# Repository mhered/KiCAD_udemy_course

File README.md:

# README.md

This repository contains [my course notes](./notes/KiCAD_notes.md) from the Udemy course [KiCAD like a Pro](https://www.udemy.com/course/kicad-like-a-pro-3e/) by Dr Peter Dalmaris, as well as several beginner friendly KiCAD projects (some of which are inspired in the course)

| Image                                                        | Name                                                         | Description                                                  | Source                                                       |
| ------------------------------------------------------------ | ------------------------------------------------------------ | ------------------------------------------------------------ | ------------------------------------------------------------ |
|            | [LED Torch](./projects/01_LED_torch/)                        | First basic PBC. Project #1 from the Udemy course [KiCAD like a Pro](https://www.udemy.com/course/kicad-like-a-pro-3e/) by Dr Peter Dalmaris | [KiCAD like a Pro](https://www.udemy.com/course/kicad-like-a-pro-3e/) |
|  | [Breadboard Power Supply](./projects/02_breadboard_power_supply/) | Project #2 from the Udemy course [KiCAD like a Pro](https://www.udemy.com/course/kicad-like-a-pro-3e/) by Dr Peter Dalmaris | [KiCAD like a Pro](https://www.udemy.com/course/kicad-like-a-pro-3e/) |
|  | [Tiny Solar Supply](./projects/03_tiny_solar_supply/)        | Project #3 from the Udemy course [KiCAD like a Pro](https://www.udemy.com/course/kicad-like-a-pro-3e/) by Dr Peter Dalmaris | [KiCAD like a Pro](https://www.udemy.com/course/kicad-like-a-pro-3e/) |
|  | [MCU Datalogger](./projects/04_MCU_datalogger/)              | Project #4 from the Udemy course [KiCAD like a Pro](https://www.udemy.com/course/kicad-like-a-pro-3e/) by Dr Peter Dalmaris | [KiCAD like a Pro](https://www.udemy.com/course/kicad-like-a-pro-3e/) |
|              | [Kinect Lite](./projects/05_kinect_lite/)                    | Hacking the Kinect - inspired by a post by Weekend Robotics from 2019 on how to turn an old Kinect into a low cost and compact USB-C powered RGBD sensor | [Weekend Robotics]( https://medium.com/robotics-weekends/how-to-turn-old-kinect-into-a-compact-usb-powered-rgbd-sensor-f23d58e10eb0) and [vojtapl's Github](https://github.com/vojtapl/xbox360-kinect-lite) |
|         | [Pico IoT Thingy](./projects/06_pico_IoT_thingy/)            | Raspberry PICO IoT device on 4-layer PCB with sensors and more b- based on a YouTube tutorial by morten | [YouTube tutorial ](https://www.youtube.com/watch?v=tCulctQqdhM) by morten |
|                 | [MSPM0](./projects/07_MSPM0/)                                | Texas Instruments MSPM0-based hardware (USB, power, MCU, peripherals) based on a YouTube tutorial by Phil's Lab | [YouTube tutorial](https://www.youtube.com/watch?v=O-zNn5k5Bn4) by Phil's Lab |
|                   | [Reskin](./projects/08_reskin/)                              | 5X Reskin pressure sensor for robotics                       | [raunaqbhirangi's Github](https://github.com/raunaqbhirangi/reskin_sensor/tree/main/circuits) |

### ⚠️ Libraries included

This repository follows (mostly) [these recommendations](./notes/recommended_libraries_setup_in_KiCAD_repo.md) to facilitate that everything needed to replicate these projects travels with the repo 

### ⚠️ Git LFS Required

This repository uses [Git Large File Storage (Git LFS)](https://git-lfs.com/) to handle large files (mainly for CAD models, and zipped gerber files).

If you clone the repo without Git LFS, large files will appear as tiny pointer files instead of the real content.

### Setup
1. Install Git LFS on your system:

   ```bash
   sudo apt install git-lfs
   ```

2. Run once on your machine to set it up for your user account:
   ```bash
   git lfs install
   ```

3. Clone the repository as usual:

   ```bash
   git clone https://github.com/mhered/KiCAD_udemy_course.git
   ```

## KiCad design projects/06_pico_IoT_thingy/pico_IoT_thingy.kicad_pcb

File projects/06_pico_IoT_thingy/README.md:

# README.md

[TOC]

Design of a Raspberry PICO IoT device on 4-layer PCB with sensors and more. Ref. https://www.youtube.com/watch?v=tCulctQqdhM by morten

Features:

* Raspberry Pi Pico (W)
* RS485 / MOD-bus interface
*  DIP-switch for MOD-bus address selection 
* SHT31-DIS high precision temperature and humidity sensor. I used P version (with protective film for reflow)
* QWIIC connector 
* Reset Button  
* User Button 
* User RGB LED 
* 2x5 pin SPI bus expansion header   
* Power relay (230V - 16A)      
* Wide range input voltage +8V to 24V DC 

For the mechanical side of things:

* 4-layer board design
* Size 80x80mm
* 4 x 3.2mm mounting holes 

## My notes on components

TRACO Power TSR-1 2450 - DC-DC step-down (buck) regulator (replaces 78xx linear regulators) with a single 5V output at up to 1A

DC power jack > takes nominal 12V but accepts a wide range of input voltage

1A polyfuse to protect input - 1.1A hold current polyfuse > selected MF-R110 (TH) / MF-SM100-2 (SMT)

diode 24V tranzorb (used **SMAJ24A**)

3.3V bar: 

* Check out this guide [Hardware design with RP2040](https://pip-assets.raspberrypi.com/categories/814-rp2040/documents/RP-008279-DS-1-hardware-design-with-rp2040.pdf)  guide ([local copy](./assets/RP-008279-DS-1-hardware-design-with-rp2040.pdf))
* LDO for 3.3.V - TLV1117-33IDCYR 800mA Low-Dropout Linear Regulator, 3.3V fixed output, SOT-223-4

Pico W:

* 1N5819 40V 1A Schottky Barrier Rectifier Diode, DO-41 to protect Vin > replaced by **SS14** iaw ChatGPT the **SS14** is a standard SMD analog (same **1 A / 40 V** rating in a DO-214AC package)

Relay:

* diode in reverse: LL4148 > replaced by **SS14**

Transceiver: THVD1406DR transceiver (made custom symbol) instead of MAX3485 

## Schematics

Screw terminal model from here: https://grabcad.com/library/pcb-mount-screw-terminal-block-connectors-1 converted to STEP using Onshape (spam, nonstd pwd).

Why is he using 4 wires for RS485? See: https://www.seeedstudio.com/blog/2021/03/18/how-rs485-works-and-how-to-implement-rs485-into-industrial-control-systems/

Initial placement of components (before routing):

## v1.2

first proto sent to production

Known issues:

* silkscreen missing connector labels, project name and version

## Testing the first proto (v1.2)

Test sequence

1.  To power up, connect input to Jack (12VDC nominal, 6.5-36VDC allowed)
    * PWR LED lights up (GREEN)
    * check 5V between GND and 5V
    * check 3.3v between GND and 3V3

2.  Flash micropython using SWD

3.  upload scripts using RS485

4.  run full test suite: [pico_IoT_thingy — testing Firmware](./Micropython/README.md)

### Notes on implementation

I had to do some research to understand the design in detail in order to write testing firmware. Below are my notes on implementation and the findings after conducting testing of the first proto (v1.2)

#### Pico W pinout

Reference needed to address pins via software

#### SWD connector (J3)

Exposes the DEBUG interface of the Pico. It allows flashing micropython but it is not practical to upload firmware:

* SWCLK

* SWDIO

* GND 

**TO DO:** 

- [ ] **test SWD connector for flashing firmware (not yet tested, so far flashing done over USB)**

#### Relay

When Pin 15 (GPIO11) (/RELAY net) is set to HIGH:

- the 16A 250VAC relay switches
- the yellow LED (**D5**) labelled **OUT** lights up

Findings during testing:

- Relay **NO** and **NC** pins are labelled incorrectly -> need to be swapped

- YELLOW LED **D5** was powering up but relay did not work > confirmed  that the circuit in v1.2 was designed for the monostable (non latching) version of the relay (Ref. RT314005) but the reference used was a bistable realy (Ref. RT314A05) so it could not work. A bistable would require an H-bridge to reverse polarity (!!). Replaced the RT314A05 in the proto and confirmed the board works well with the correct relay RT314005.

**TO DO:**

- [ ] **Swap incorrect NO and NC labels in future version** 
- [ ] **Update RT314005 symbol and footprint in future version**

#### User-programmable button

Pressing the button sets GPIO13 (/SW net) HIGH. This button was used as primary user input in testing firmware.

#### Reset button

 Pressing the button sets Pin 30 (/RUN net) LOW and resets the Pico

Not yet tested.

**TO DO:**

- [ ] **Test RESET button** 

#### User RGB LED

Findings: 

* Board v1.2 assumed an RGB LED (**D8**) of **RGBA** LED type. The actual component I have was of **BGRA** type, with the following pinout:

  - LED Pin 1 is BLUE

  - LED Pin 2 is GREEN

  - LED Pin3 is RED

  - LED Pin 4 is ANODE

  Consequently pin assignments were updated via firmware:

  * Pin 21 (GPIO16 -> RED 
  * Pin 22 (GPIO17) -> GREEN 
  * Pin 24 (GPIO18) -> BLUE

  Note these pins do not need to be ADC, PWM can be used to smoothly control LED color 

- Note: RGB LED (**D8**) should be installed such that the green mark is pointing downwards, see images. During testing of the proto it was found incorrectly installed (rotated 180 degrees), resulting in BLUE and RED colors swapped and GREEN color dead -> Fixed in the proto. 

|  |  |
| ------------------------------------------------------------ | ------------------------------------------------------------ |

**TO DO:**

- [x] **In future version update D8 symbol and nets / pin assignments as follows:** 
  * **GPIO16 (pin 21) -> RGB LED_R** 
  * **GPIO17 (pin 22) -> RGB LED_G** 
  * **GPIO18 (pin 24) -> RGB LED_B** 

#### RS485 transceiver and connector

RS485 transceiver (ref THVD1406DR ) **IC1** connects to the UART interface of Pico W:

* Pin 1 (GPI00 / UART0_TX) -> D

* Pin 2 (GPI01 / UART0_RX) -> R

Note: SHDN and RE are together set to HIGH which iaw the datasheet of the THVD1406DR transceiver enables Auto-direction mode which allows controlling driver and receiver using the data input pin D 

Questions: 

- PRELIMINARY ANSWERS: What is **J7** connector?  A jumper to activate the 120R resistor connecting A and B. Is this the termination resistor? Probably yes. How does it alter behaviour of RS485 connector? Should be installed only if this component is at the end of the line.
- what is the MOD-bus address selected with the DIP switch for? How does the RS485 transceiver know ?

Findings during testing:

* Connecting to RS485 dongle:

  - dongle A+ connects to board **A-**

  - dongle B- to board **B+**

**TO DO:** 

- [ ] **Review RS485 labels (A+ or - / B+ or -) to avoid confusion**
- [ ] **Replace J5 RS485 connector: use 4-pin 2.54mm pitch screw terminal instead of 5mm pitch**
- [ ] **test MOD-bus address selection with the DIP switch and RS485 protocol**
- [ ] **Expose UART: Not having UART exposed makes it difficult to upload software on the Pico. Hacked it shaving off the rubber from a microUSB connector to connect directly the Pico to PC via USB.**

#### DIP switch

* GPIO19 -> DIP4
* GPIO20 -> DIP3
* GPIO21 -> DIP2
* GPIO22 -> DIP1

**TO DO:** 

- [ ] **Question: which way is 1 / 0 ?**

#### SPI connector (J6)

* Pin 4 (GPI02 / SPI0_SCK) labelled **SCK**
* Pin 5 (GPI03 / SPI0_TX) MOSI labelled 
* Pin 6 (GPI04 / SPI0_RX) MISO labelled  
* Pin 7 (GPI05 / SPI0_CSn) labelled **CS**

Also exposed: 3V3, GND, ADC0/GPIO26 and ADC1/GPIO27

**TO DO:** 

- [ ] **Test SPI communication with PC, current firmware only checks loop between Tx and Rx**

#### I2C interface

I2C temperature sensor SHT31 (**U2**) and QWIIC connector **J2** connect to PicoW via I2C interface:

* SDA: Pin 9 (GPI06 / I2C1_SDA)
* SCL: Pin 10 (GPI07 / I2C1_SCL)

#### Resistor (R5)

Leave **R5** 0Ohm resistor unpopulated so Pico W will not power the 3V3 bar

If R5 is populated Pico W powers the 3V3 bar and may drive too much current (not tested)

#### Wifi

Findings:

Wifi was not working on USB-C Pico W. Replaced to check if it was a faulty unit or a fake component 

- "fake component" (Pico W wih USB-C connector) does not have CYW43 but an ESP instead, does not work with std libraries, requires low level syntax.
- additionally the first Fake Pico W was apparently faulty. 

**TO DO:** 

- [ ] **update firmware to output logging to web server / webrepl**
- [ ] **confirm if first Fake Pico W is faulty**

## v1.4 (WIP)

Tests pending:

- [ ] test RESET button
- [ ] test flashing via SWD
- [ ] test SPI comms
- [ ] test MOD-bus address selection with the DIP switch and RS485 protocol / which way is 1 / 0 ?
- [ ] update firmware to output logging to web server / webrepl
- [ ] confirm if first Fake Pico W is faulty

Fixes:

- [x] Update silkscreen to add missing labels: connector pinout (SWD, SPI, RS485), 12V nominal input voltage, project name and version
- [x] Swap incorrect **NO** and **NC** labels for relay 
- [ ] Review RS485 labels (A+ or - / B+ or -) to avoid confusion
- [ ] Replace RT314A05 symbol and footprint by RT314005
- [x] update RGB LED D8 symbol and nets / pin assignments for BGRA type as follows:
  * GPIO16 (pin 21) -> RGB LED_R 
  * GPIO17 (pin 22) -> RGB LED_G 
  * GPIO18 (pin 24) -> RGB LED_B
- [ ] Consider moving the PicoW footprint to avoid the clash with the USB connector  
- [ ] Replace J5 RS485 connector: use 4-pin 2.54mm pitch screw terminal instead of 5mm pitch
- [ ] Expose UART: Not having UART exposed makes it difficult to upload software on the Pico. Hacked it shaving off the rubber from a microUSB connector to connect directly the Pico to PC via USB.

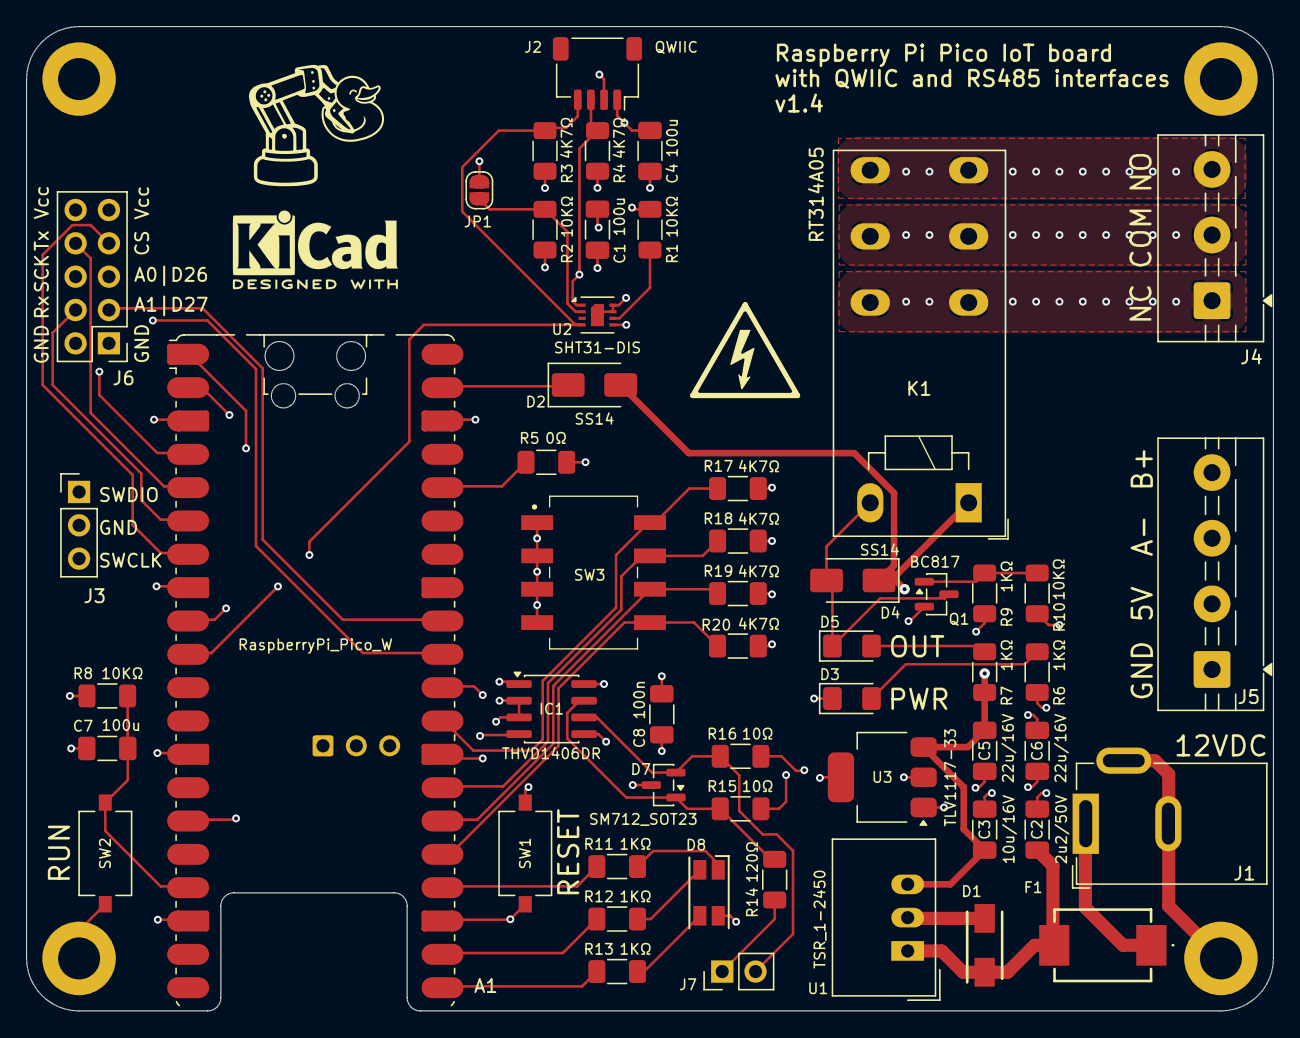
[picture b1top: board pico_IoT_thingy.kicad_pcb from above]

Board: 4 copper layers, 95.0 x 75.0 mm, 60 parts (0 on the bottom side), 46 nets.

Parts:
A1: RaspberryPi_Pico_W; RaspberryPi_Pico_W_SMD_HandSolder
C1, C4, C7: 100u; C_1206_3216Metric_Pad1.33x1.80mm_HandSolder
C2: 2u2/50V; C_1206_3216Metric_Pad1.33x1.80mm_HandSolder
C3: 10u/16V; C_1206_3216Metric_Pad1.33x1.80mm_HandSolder
C5, C6: 22u/16V; C_1206_3216Metric_Pad1.33x1.80mm_HandSolder
C8: 100n; C_1206_3216Metric_Pad1.33x1.80mm_HandSolder
D1: SMAJ24A; DIOM5127X229N
D2, D4: SS14; D_SMA
D3: GREEN; LED_1206_3216Metric_Pad1.42x1.75mm_HandSolder
D5: YELLOW; LED_1206_3216Metric_Pad1.42x1.75mm_HandSolder
D7: SM712_SOT23; SOT-23
D8: LED_RGBA; LED_RGB_1210
F1: 1A; MFSM1002
H1, H2, H3, H4: MountingHole_Pad; MountingHole_3.2mm_M3_DIN965_Pad
HIGHVOLT_LOGO: MH_Symbol_HighVoltage_Triangle_8x7mm_Silkscreen
IC1: THVD1406DR; SOIC-8_3.9x4.9mm_P1.27mm
J1: Barrel_Jack_Switch; BarrelJack_GCT_DCJ200-10-A_Horizontal
J2: QWIIC; JST_SH_SM04B-SRSS-TB_1x04-1MP_P1.00mm_Horizontal
J3: Conn_01x03; PinHeader_1x03_P2.54mm_Vertical
J4: Screw_Terminal_01x03; TerminalBlock_MaiXu_MX126-5.0-03P_1x03_P5.00mm
J5: Screw_Terminal_01x04; TerminalBlock_MaiXu_MX126-5.0-04P_1x04_P5.00mm
J6: Conn_02x05_Odd_Even; PinHeader_2x05_P2.54mm_Vertical
J7: Conn_01x02; PinHeader_1x02_P2.54mm_Vertical
JP1: SolderJumper_2_Open; SolderJumper-2_P1.3mm_Open_RoundedPad1.0x1.5mm
K1: RT314A05; Relay_SPDT_Schrack-RT1-16A-FormC_RM5mm
KICAD_LOGO: KiCad-Logo2_5mm_SilkScreen
Q1: BC817; SOT-23
R1, R2, R8, R10: 10KΩ; R_1206_3216Metric_Pad1.30x1.75mm_HandSolder
R3, R4, R17, R18, R19, R20: 4K7Ω; R_1206_3216Metric_Pad1.30x1.75mm_HandSolder
R5: 0Ω; R_1206_3216Metric_Pad1.30x1.75mm_HandSolder
R6, R7, R9, R11, R12, R13: 1KΩ; R_1206_3216Metric_Pad1.30x1.75mm_HandSolder
R14: 120Ω; R_1206_3216Metric_Pad1.30x1.75mm_HandSolder
R15, R16: 10Ω; R_1206_3216Metric_Pad1.30x1.75mm_HandSolder
SW1, SW2: SW_SPST; SW_Tactile_SPST_NO_Straight_CK_PTS636Sx25SMTRLFS
SW3: SW_DIP_x04; 2194MST
U1: TSR_1-2450; Converter_DCDC_TRACO_TSR-1_THT
U2: SHT31-DIS; Sensirion_DFN-8-1EP_2.5x2.5mm_P0.5mm_EP1.1x1.7mm
U3: TLV1117-33; SOT-223-3_TabPin2

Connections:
+3V3: C1.1, C4.1, C6.1, C8.1, D8.4 (A), IC1.2 (~RE), IC1.3 (~SHDN), IC1.8 (VCC), J2.2, J6.9, J6.10, JP1.2 (B), R1.1, R3.1, R4.1, R5.1, R6.1, R8.1, R17.1, R18.1, R19.1, R20.1, U2.5 (VDD), U3.2 (VO)
+5V: C3.1, C5.1, D2.2 (A), D4.1 (K), J5.2, K1.A1, R7.1, U1.3 (Vout), U3.3 (VI)
+24V: C2.1, D1.1 (K), F1.2, U1.1 (Vin)
/A: J5.3, R16.2
/B: J5.4, R15.2
/DIP1: A1.29 (GPIO22), R17.2, SW3.8
/DIP2: A1.27 (GPIO21), R18.2, SW3.7
/DIP3: A1.26 (GPIO20), R19.2, SW3.6
/DIP4: A1.25 (GPIO19), R20.2, SW3.5
/GPIO26: A1.31 (GPIO26_ADC0), J6.5
/GPIO27: A1.32 (GPIO27_ADC1), J6.3
/I2C1_SCL: A1.10 (GPIO7), J2.4, R3.2, U2.4 (SCL)
/I2C1_SDA: A1.9 (GPIO6), J2.3, R4.2, U2.1 (SDA)
/LED_B: A1.24 (GPIO18), R11.1
/LED_G: A1.22 (GPIO17), R12.1
/LED_R: A1.21 (GPIO16), R13.1
/LOAD_COM: J4.2, K1.11
/LOAD_NC: J4.1, K1.12
/LOAD_NO: J4.3, K1.14
/RELAY: A1.15 (GPIO11), R9.1
/RUN: A1.30 (RUN), SW1.2 (B)
/SPI0_CSn: A1.7 (GPIO5), J6.7
/SPI0_RX: A1.6 (GPIO4), J6.4
/SPI0_SCK: A1.4 (GPIO2), J6.6
/SPI0_TX: A1.5 (GPIO3), J6.8
/SW: A1.17 (GPIO13), C7.1, R8.2, SW2.2 (B)
/UART0_RX: A1.2 (GPIO1), IC1.1 (R)
/UART0_TX: A1.1 (GPIO0), IC1.4 (D)
GND: A1.3 (GND), A1.8 (GND), A1.13 (GND), A1.18 (GND), A1.23 (GND), A1.28 (GND), A1.38 (GND), A1.D2 (GND), C1.2, C2.2, C3.2, C4.2, C5.2, C6.2, C7.2, C8.2, D1.2 (A), D3.1 (K), D7.3 (common), H1.1 (1_1), H3.1 (1_1), H4.1 (1_1), IC1.5 (GND), J1.2, J1.3, J2.1, J3.2, J5.1, J6.1, J6.2, Q1.2 (E), R2.2, R10.2, SW1.1 (A), SW2.1 (A), SW3.1, SW3.2, SW3.3, SW3.4, U1.2 (GND), U2.7 (R), U2.8 (VSS), U2.9 (VSS), U3.1 (GND)
unnamed: A1.36 (3V3), R5.2
unnamed: A1.D1 (SWCLK), J3.3
unnamed: A1.D3 (SWDIO), J3.1
unnamed: A1.39 (VSYS), D2.1 (K)
unnamed: D3.2 (A), R6.2
unnamed: D4.2 (A), D5.1 (K), K1.A2, Q1.3 (C)
unnamed: D5.2 (A), R7.2
unnamed: D7.1 (A1), IC1.7 (B), R14.2, R15.1
unnamed: D7.2 (A2), IC1.6 (A), J7.2, R16.1
unnamed: D8.1 (BK), R11.2
unnamed: D8.2 (GK), R12.2
unnamed: D8.3 (RK), R13.2
unnamed: F1.1, J1.1
unnamed: J7.1, R14.1
unnamed: JP1.1 (A), R2.1, U2.2 (ADDR)
unnamed: Q1.1 (B), R9.2, R10.1
unnamed: R1.2, U2.6 (~RESET)

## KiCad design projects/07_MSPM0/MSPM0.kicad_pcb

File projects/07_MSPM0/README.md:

# README.md

Based on [KiCad 9 Hardware Design Tutorial (TI MSPM0)](https://www.youtube.com/watch?v=O-zNn5k5Bn4) Youtube tutorial by Phil's Lab

## Microcontroller MSPM0G3507SPTR

Texas Instruments middle of the range MCU from MSP family:  80MHz Arm Cortex-M0+ MCU with 128KB flash 32KB SRAM 2x4Msps ADC, DAC, 3xCOMP, 2xOPA, CAN-FD, MATHA

(four UART, two I2C, two SPI, and CAN 2.0/FD)

https://www.ti.com/product/MSPM0G3507/part-details/MSPM0G3507SPTR

https://www.ti.com/lit/ds/symlink/mspm0g3507.pdf

## Project modified to add 9DOF

Two chips connected via I2C:

A 6DOF IMU: 

LSM6DSR - iNEMO inertial module: always-on 3D accelerometer and 3D gyroscope

LCSC# C784817

Datasheet: https://www.lcsc.com/datasheet/C784817.pdf

Arduino library: https://github.com/stm32duino/LSM6DSR

A 3-axis magnetic sensor 

MMC5983MA - 3-axis magnetic sensor with on-chip signal processing and integrated I2C/SPI bus 

LCSC# C404329

Datasheet: https://www.lcsc.com/datasheet/C404329.pdf

Add axes to silkscreen

Refer to:

https://www.memsic.com/magnetometer-5

PCB layout guidance

https://www.digikey.bg/en/pdf/m/memsic/magnetic-sensor-hardware-guideline

https://www.nxp.com/docs/en/application-note/AN4247.pdf

Arduino library: https://github.com/sparkfun/SparkFun_MMC5983MA_Magnetometer_Arduino_Library

## WIP

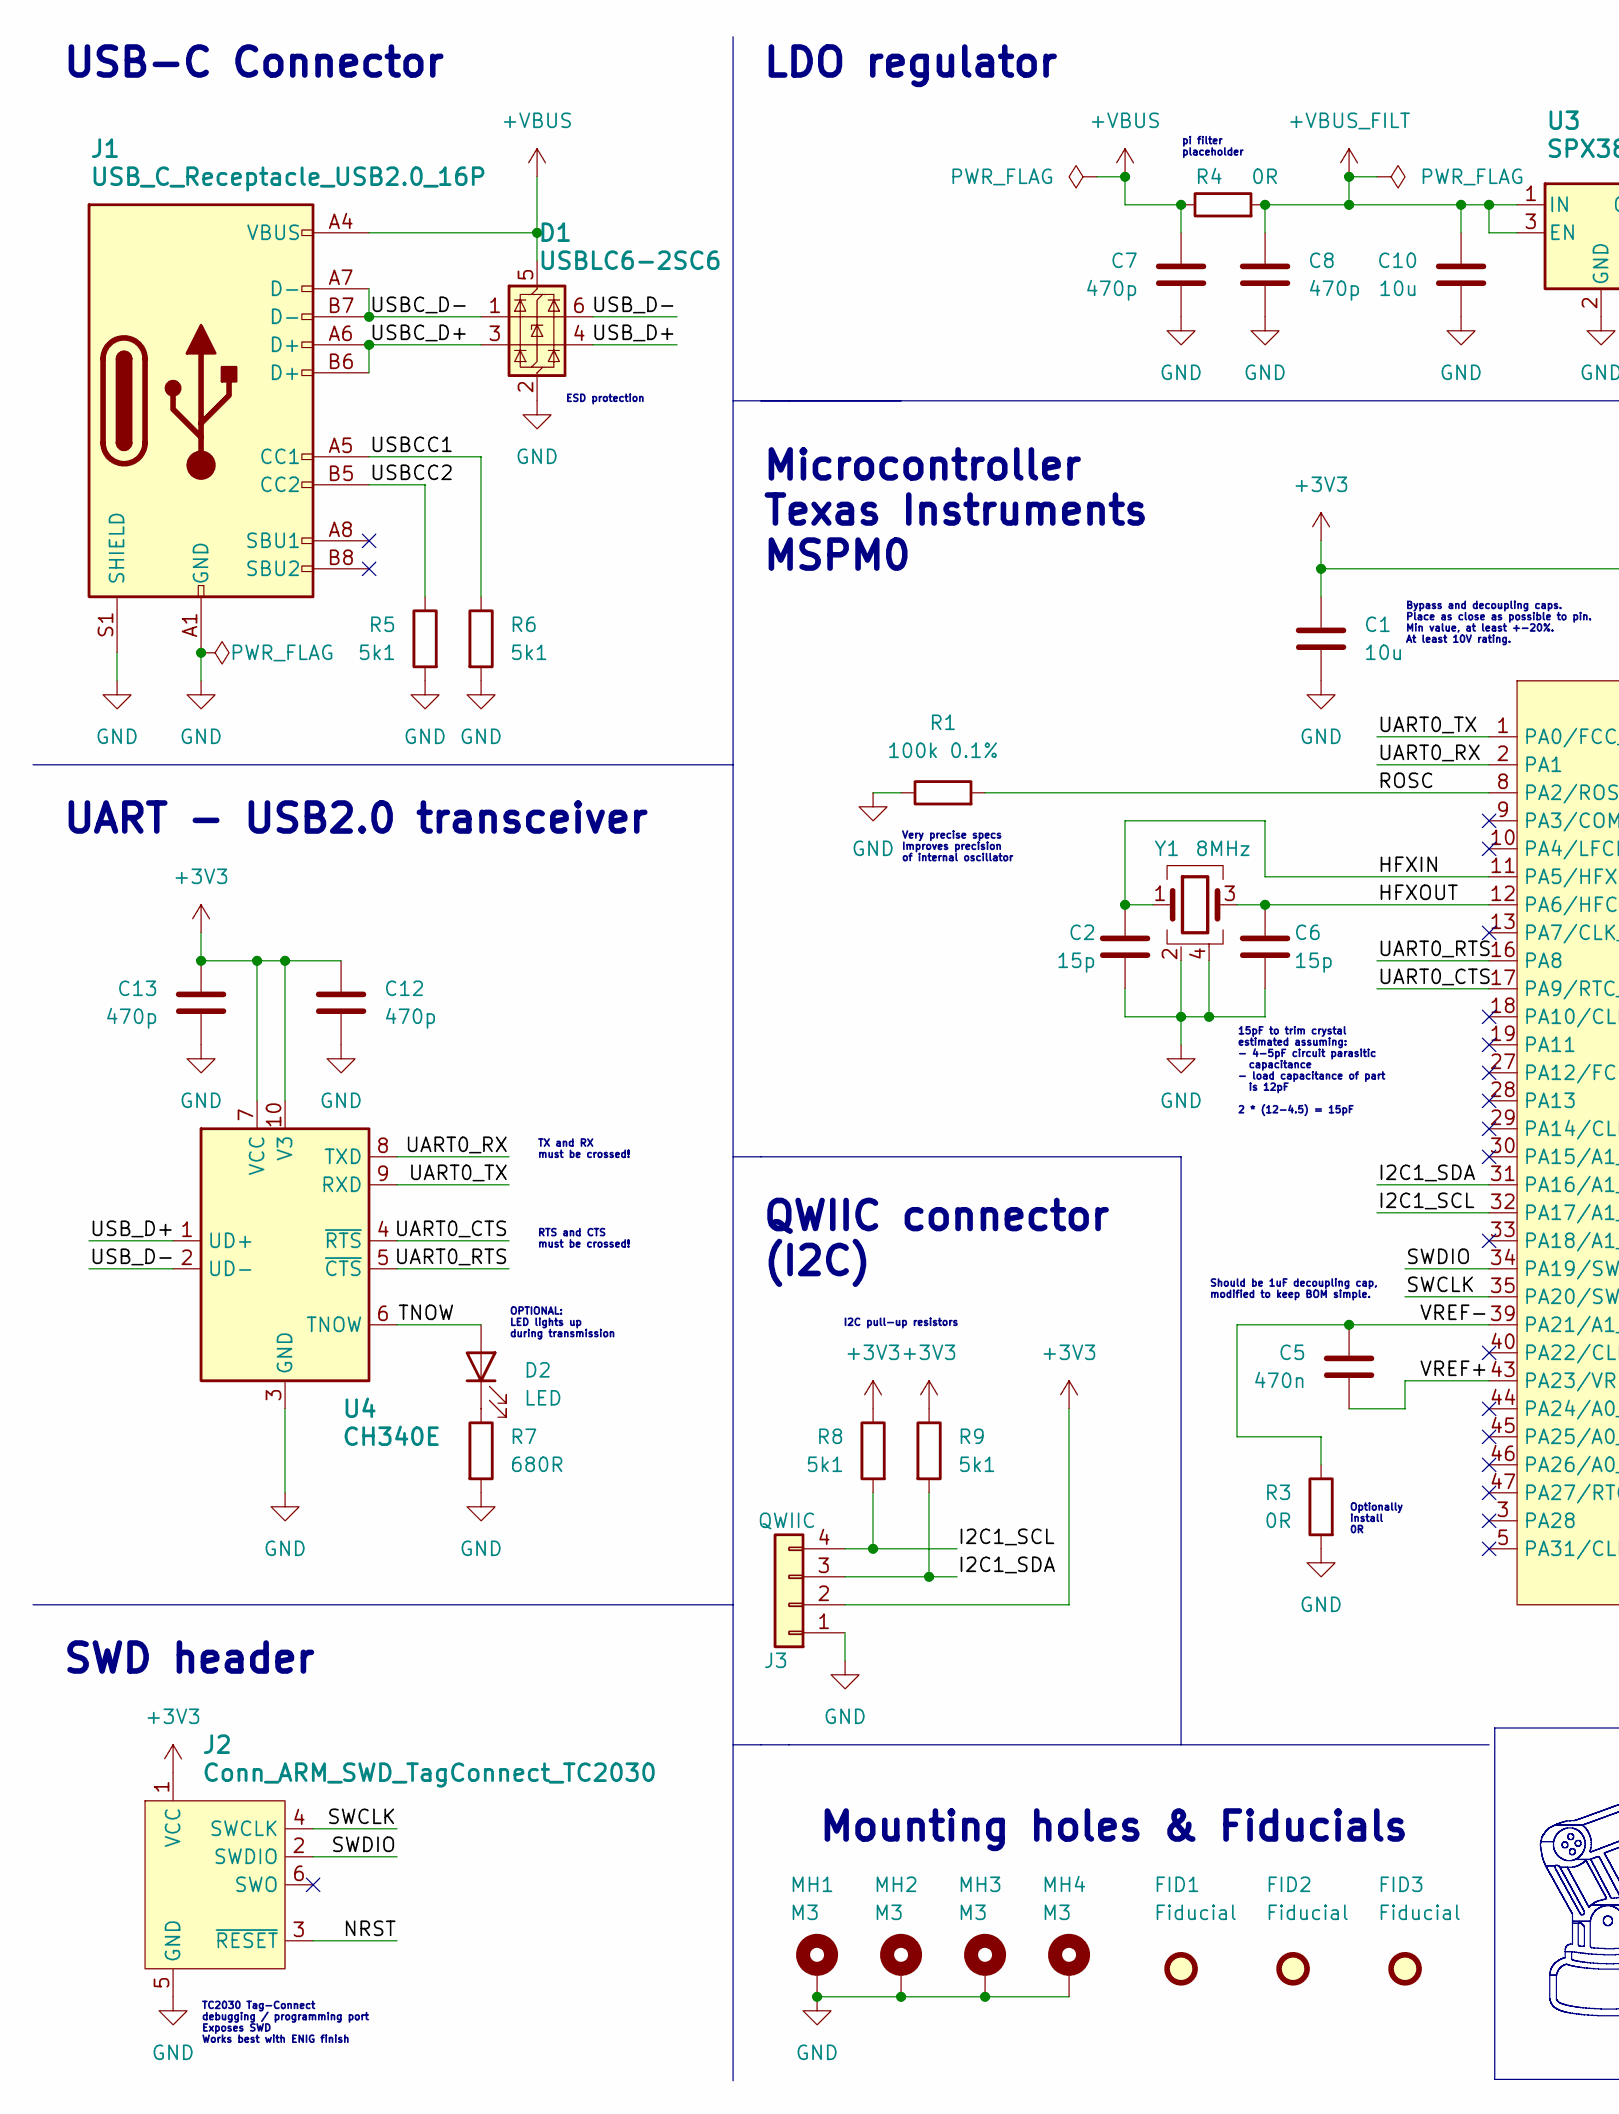
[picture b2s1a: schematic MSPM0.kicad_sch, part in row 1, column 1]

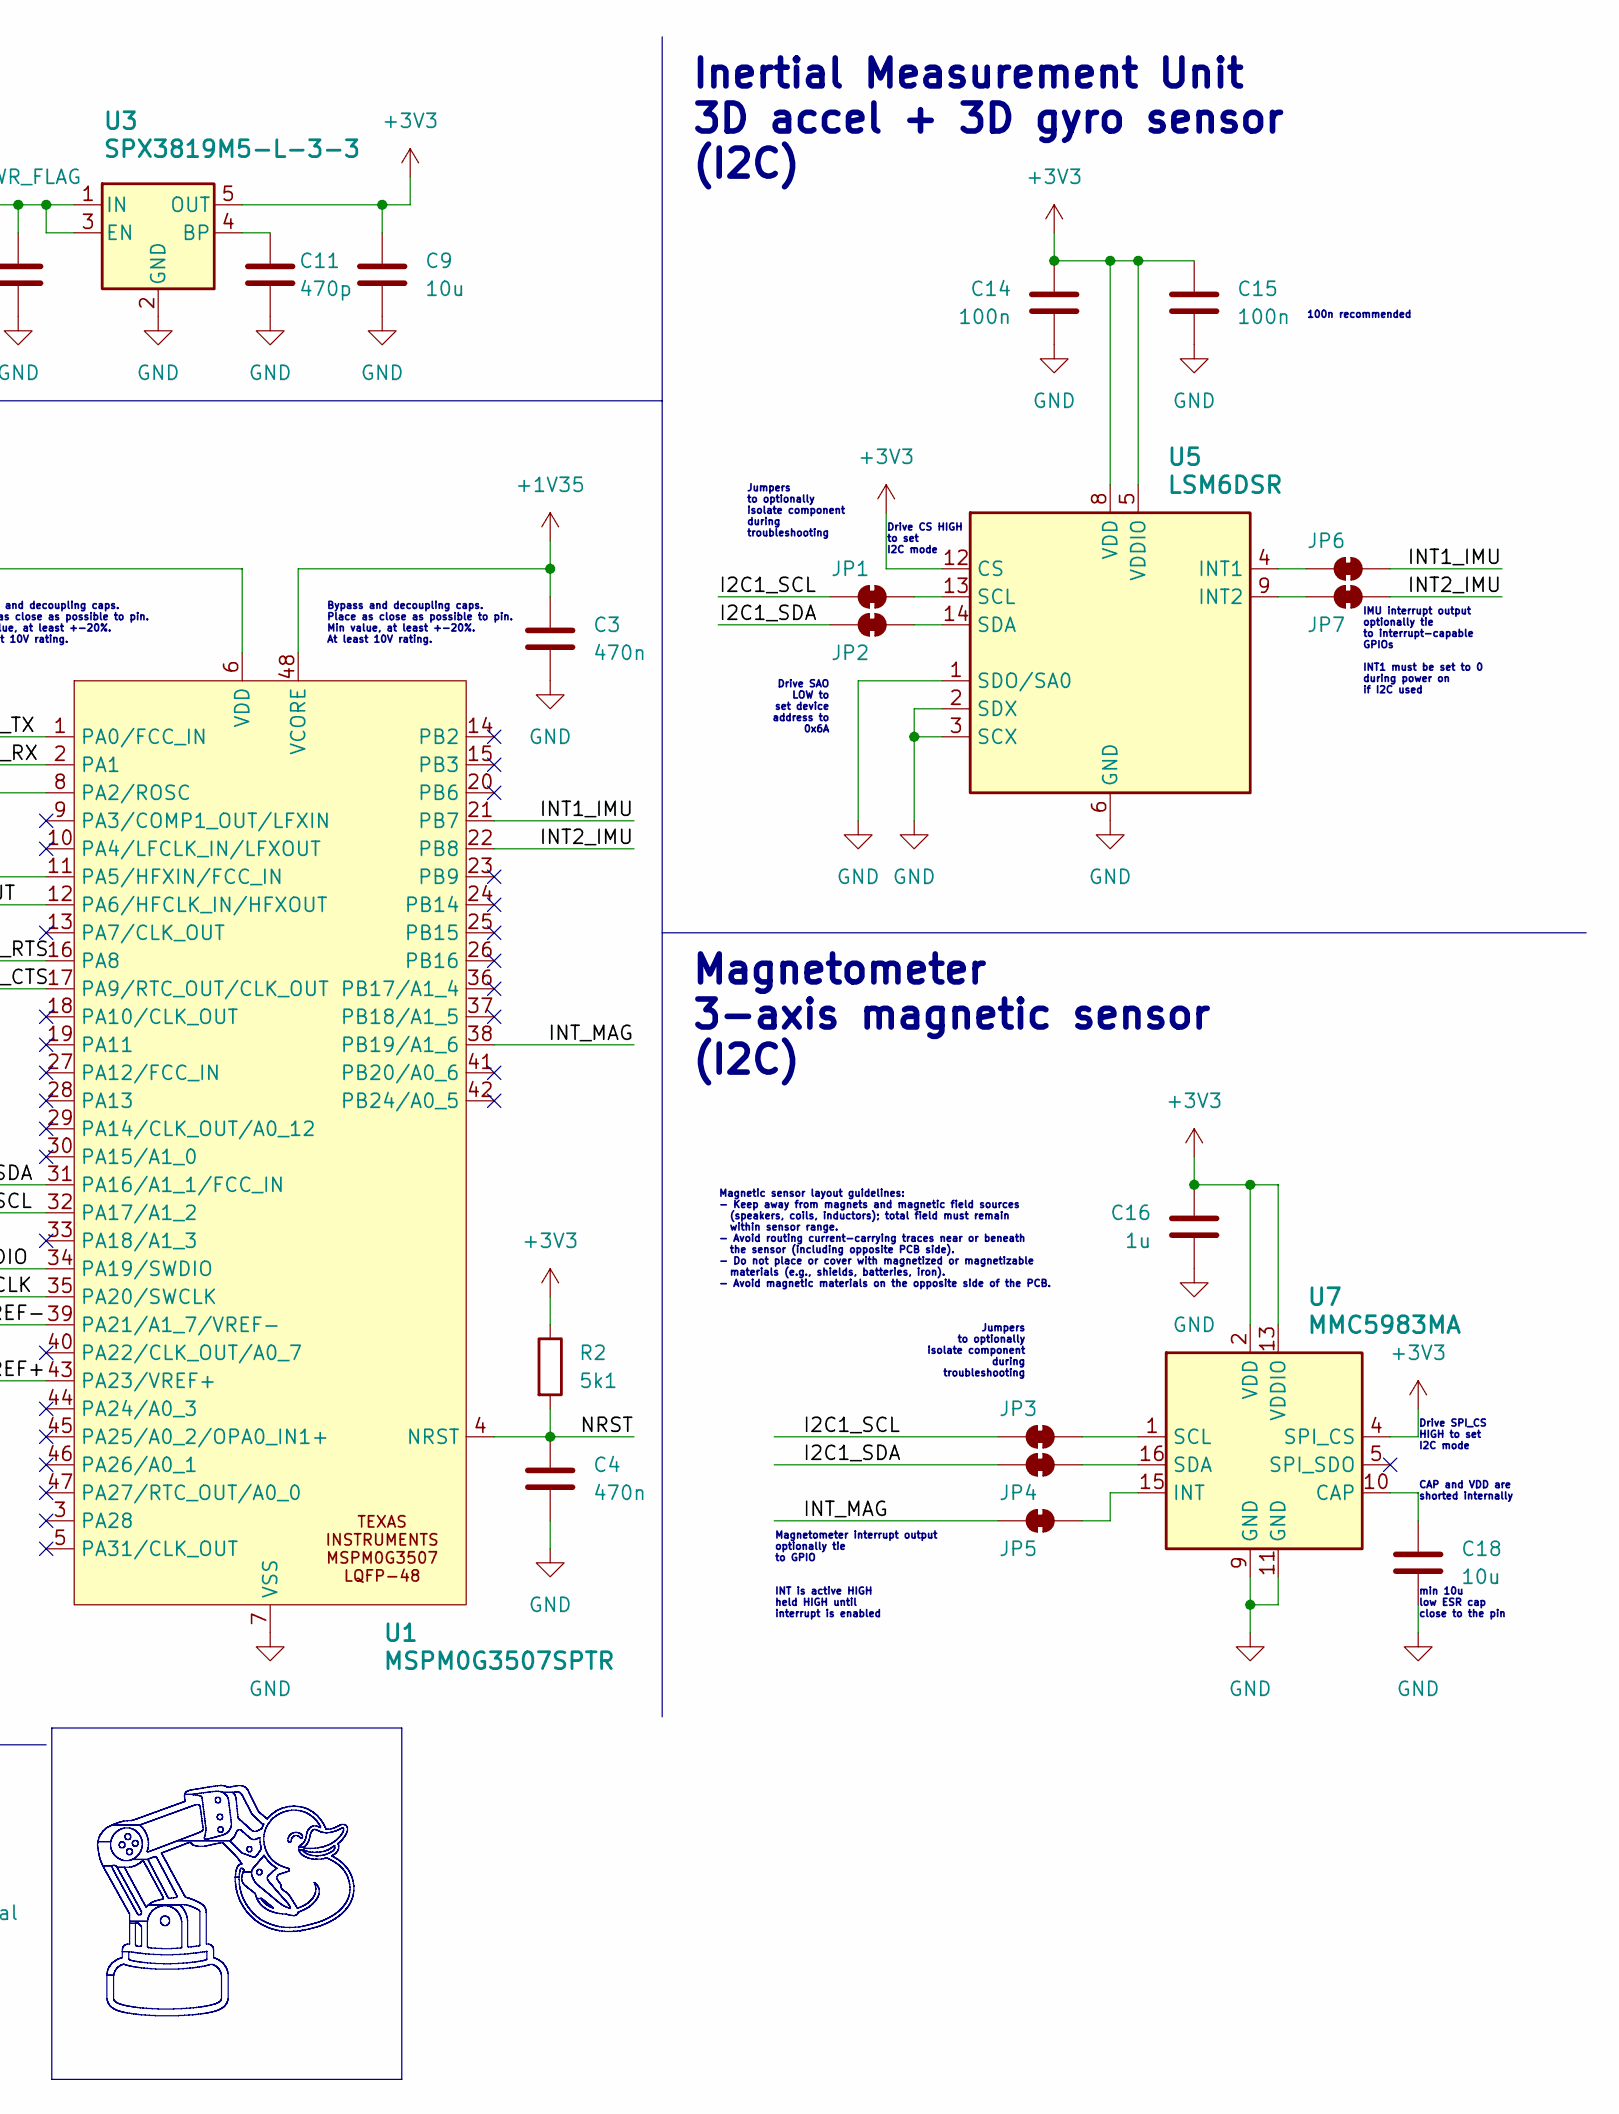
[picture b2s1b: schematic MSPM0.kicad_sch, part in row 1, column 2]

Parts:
C1, C9, C10, C18: 10u; C_1206_3216Metric_Pad1.33x1.80mm_HandSolder
C2, C6: 15p; C_0603_1608Metric_Pad1.08x0.95mm_HandSolder
C3, C4, C5: 470n; C_0603_1608Metric_Pad1.08x0.95mm_HandSolder
C7, C8, C11, C12, C13: 470p; C_0603_1608Metric_Pad1.08x0.95mm_HandSolder
C14, C15: 100n; C_0603_1608Metric_Pad1.08x0.95mm_HandSolder
C16: 1u; C_1206_3216Metric_Pad1.33x1.80mm_HandSolder
D1: USBLC6-2SC6; SOT-23-6_Handsoldering; LCSC PN C2687116
D2: LED; LED_1206_3216Metric_Pad1.42x1.75mm_HandSolder
FID1, FID2, FID3: Fiducial; Fiducial_1mm_Mask2mm
J1: USB_C_Receptacle_USB2.0_16P; USB_C_Receptacle_G-Switch_GT-USB-7010ASV; LCSC PN C2988369
J2: Conn_ARM_SWD_TagConnect_TC2030; Tag-Connect_TC2030-IDC-FP_2x03_P1.27mm_Vertical
J3: QWIIC; JST_SH_SM04B-SRSS-TB_1x04-1MP_P1.00mm_Horizontal; Mouser Ref aliexpress
JP1, JP2, JP3, JP4, JP5, JP6, JP7: SolderJumper_2_Bridged; SolderJumper-2_P1.3mm_Bridged_RoundedPad1.0x1.5mm
MH1, MH2, MH3, MH4: M3; MountingHole_3.2mm_M3_Pad_Via
R1: 100k 0.1%; R_0603_1608Metric_Pad0.98x0.95mm_HandSolder; LCSC PN C122538
R2, R5, R6, R8, R9: 5k1; R_0603_1608Metric_Pad0.98x0.95mm_HandSolder
R3: 0R; R_0603_1608Metric_Pad0.98x0.95mm_HandSolder
R4: 0R; R_0603_1608Metric_Pad0.98x0.95mm_HandSolder; LCSC PN C122538
R7: 680R; R_0603_1608Metric_Pad0.98x0.95mm_HandSolder
U1: MSPM0G3507SPTR; LQFP-48_7x7mm_P0.5mm; Manufacturer PN MSPM0G3507SPTR; LCSC PN C22362630
U3: SPX3819M5-L-3-3; SOT-23-5_HandSoldering; LCSC PN C9055
U4: CH340E; MSOP-10_3x3mm_P0.5mm; LCSC PN C99652
U5: LSM6DSR; LGA-14_3x2.5mm_P0.5mm_LayoutBorder3x4y; LCSC PN C784817
U7: MMC5983MA; LGA-16_3x3mm_P0.5mm; LCSC PN C404329
Y1: 8MHz; Crystal_SMD_3225-4Pin_3.2x2.5mm_HandSoldering; LCSC PN C2682775

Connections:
+1V35: C3.1, U1.48 (VCORE)
+3V3: C1.1, C9.1, C12.1, C13.1, C14.1, C15.1, C16.1, J2.1 (VCC), J3.2, R2.1, R8.1, R9.1, U1.6 (VDD), U3.5 (OUT), U4.7 (VCC), U4.10 (V3), U5.5 (VDDIO), U5.8 (VDD), U5.12 (CS), U7.2 (VDD), U7.4 (SPI_CS), U7.13 (VDDIO)
+VBUS: C7.1, D1.5 (VBUS), J1.A4 (VBUS), J1.A9 (VBUS), J1.B4 (VBUS), J1.B9 (VBUS), R4.1
+VBUS_FILT: C8.1, C10.1, R4.2, U3.1 (IN), U3.3 (EN)
/HFXIN: C2.1, U1.11 (PA5/HFXIN/FCC_IN), Y1.1
/HFXOUT: C6.1, U1.12 (PA6/HFCLK_IN/HFXOUT), Y1.3
/I2C1_SCL: J3.4, JP1.1 (A), JP3.1 (A), R8.2, U1.32 (PA17/A1_2)
/I2C1_SDA: J3.3, JP2.1 (A), JP4.1 (A), R9.2, U1.31 (PA16/A1_1/FCC_IN)
/INT1_IMU: JP6.2 (B), U1.21 (PB7)
/INT2_IMU: JP7.2 (B), U1.22 (PB8)
/INT_MAG: JP5.1 (A), U1.38 (PB19/A1_6)
/NRST: C4.1, J2.3 (~RESET), R2.2, U1.4 (NRST)
/ROSC: R1.2, U1.8 (PA2/ROSC)
/SWCLK: J2.4 (SWCLK), U1.35 (PA20/SWCLK)
/SWDIO: J2.2 (SWDIO), U1.34 (PA19/SWDIO)
/TNOW: D2.2 (A), U4.6 (TNOW)
/UART0_CTS: U1.17 (PA9/RTC_OUT/CLK_OUT), U4.4 (~RTS)
/UART0_RTS: U1.16 (PA8), U4.5 (~CTS)
/UART0_RX: U1.2 (PA1), U4.8 (TXD)
/UART0_TX: U1.1 (PA0/FCC_IN), U4.9 (RXD)
/USBCC1: J1.A5 (CC1), R6.1
/USBCC2: J1.B5 (CC2), R5.1
/USBC_D+: D1.3 (I/O2), J1.A6 (D+), J1.B6 (D+)
/USBC_D-: D1.1 (I/O1), J1.A7 (D-), J1.B7 (D-)
/USB_D+: D1.4 (I/O2), U4.1 (UD+)
/USB_D-: D1.6 (I/O1), U4.2 (UD-)
/VREF+: C5.2, U1.43 (PA23/VREF+)
/VREF-: C5.1, R3.1, U1.39 (PA21/A1_7/VREF-)
GND: C1.2, C2.2, C3.2, C4.2, C6.2, C7.2, C8.2, C9.2, C10.2, C11.2, C12.2, C13.2, C14.2, C15.2, C16.2, C18.2, D1.2 (GND), J1.A1 (GND), J1.A12 (GND), J1.B1 (GND), J1.B12 (GND), J1.S1 (SHIELD), J2.5 (GND), J3.1, MH1.1 (1_1), MH2.1 (1_1), MH3.1 (1_1), MH4.1 (1_1), R1.1, R3.2, R5.2, R6.2, R7.2, U1.7 (VSS), U3.2 (GND), U4.3 (GND), U5.1 (SDO/SA0), U5.2 (SDX), U5.3 (SCX), U5.6 (GND), U5.7 (GND), U7.9 (GND), U7.11 (GND), Y1.2 (G), Y1.4 (G)
unnamed: D2.1 (K), R7.1
unnamed: JP1.2 (B), U5.13 (SCL)
unnamed: JP2.2 (B), U5.14 (SDA)
unnamed: JP3.2 (B), U7.1 (SCL)
unnamed: JP4.2 (B), U7.16 (SDA)
unnamed: JP5.2 (B), U7.15 (INT)
unnamed: JP6.1 (A), U5.4 (INT1)
unnamed: JP7.1 (A), U5.9 (INT2)
unnamed: C11.1, U3.4 (BP)
unnamed: C18.1, U7.10 (CAP)

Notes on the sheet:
LDO regulator
Magnetometer interrupt output optionally tie to GPIO
Should be 1uF decoupling cap, modified to keep BOM simple.
Optionally install 0R
100n recommended
Drive SAO LOW to set device address to 0x6A
15pF to trim crystal estimated assuming: - 4-5pF circuit parasitic capacitance - load capacitance of part is 12pF 2 * (12-4.5) = 15pF
Microcontroller Texas Instruments MSPM0
min 10u low ESR cap close to the pin
Bypass and decoupling caps. Place as close as possible to pin. Min value, at least +-20%. At least 10V rating.
SWD header
ESD protection
TX and RX must be crossed!
CAP and VDD are shorted internally
Inertial Measurement Unit 3D accel + 3D gyro sensor (I2C)
Magnetometer 3-axis magnetic sensor (I2C)
UART - USB2.0 transceiver
Magnetic sensor layout guidelines: - Keep away from magnets and magnetic field sources (speakers, coils, inductors); total field must remain within sensor range. - Avoid routing current-carrying traces near or beneath the sensor (including opposite PCB side). - Do not place or cover with magnetized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
Jumpers to optionally isolate component during troubleshooting
QWIIC connector (I2C)
Drive SPI_CS HIGH to set I2C mode
OPTIONAL: LED lights up during transmission
pi filter placeholder
Drive CS HIGH to set I2C mode
I2C pull-up resistors
INT is active HIGH held HIGH until interrupt is enabled
USB-C Connector
Mounting holes & Fiducials
Very precise specs Improves precision of internal oscillator
TC2030 Tag-Connect debugging / programming port Exposes SWD Works best with ENIG finish
IMU interrupt output optionally tie to interrupt-capable GPIOs INT1 must be set to 0 during power on if I2C used
RTS and CTS must be crossed!

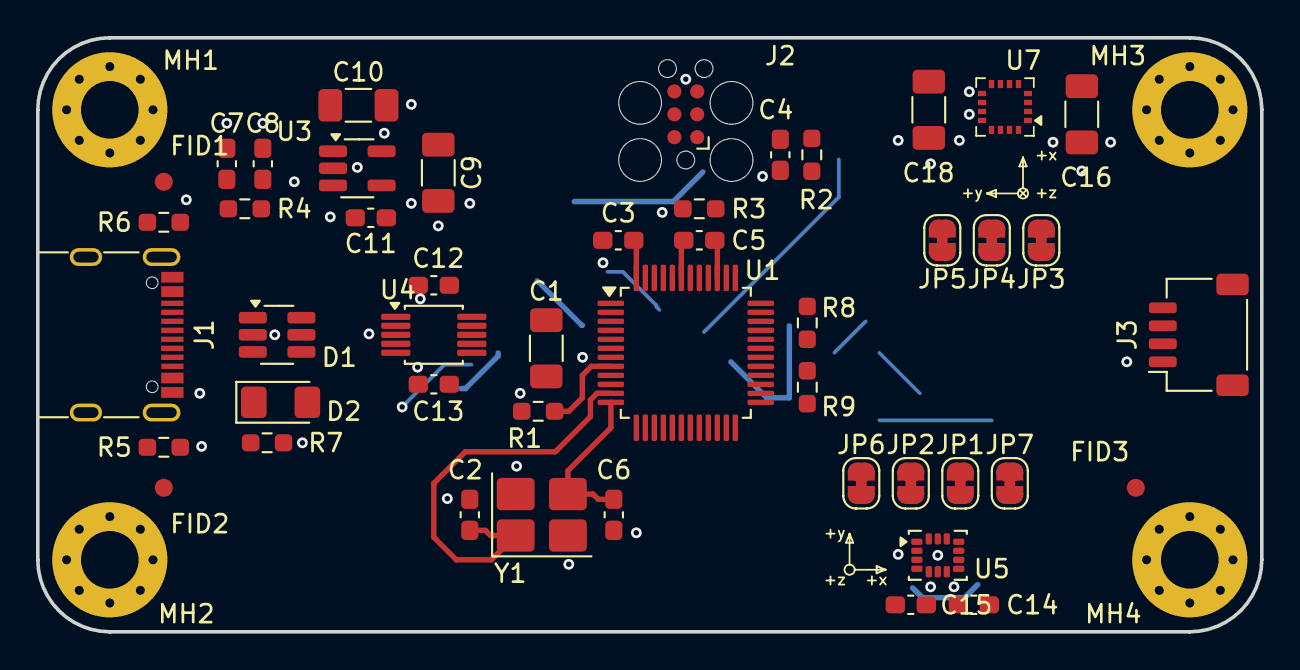
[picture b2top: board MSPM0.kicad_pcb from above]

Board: 2 copper layers, 68.0 x 33.0 mm, 51 parts (0 on the bottom side), 39 nets.

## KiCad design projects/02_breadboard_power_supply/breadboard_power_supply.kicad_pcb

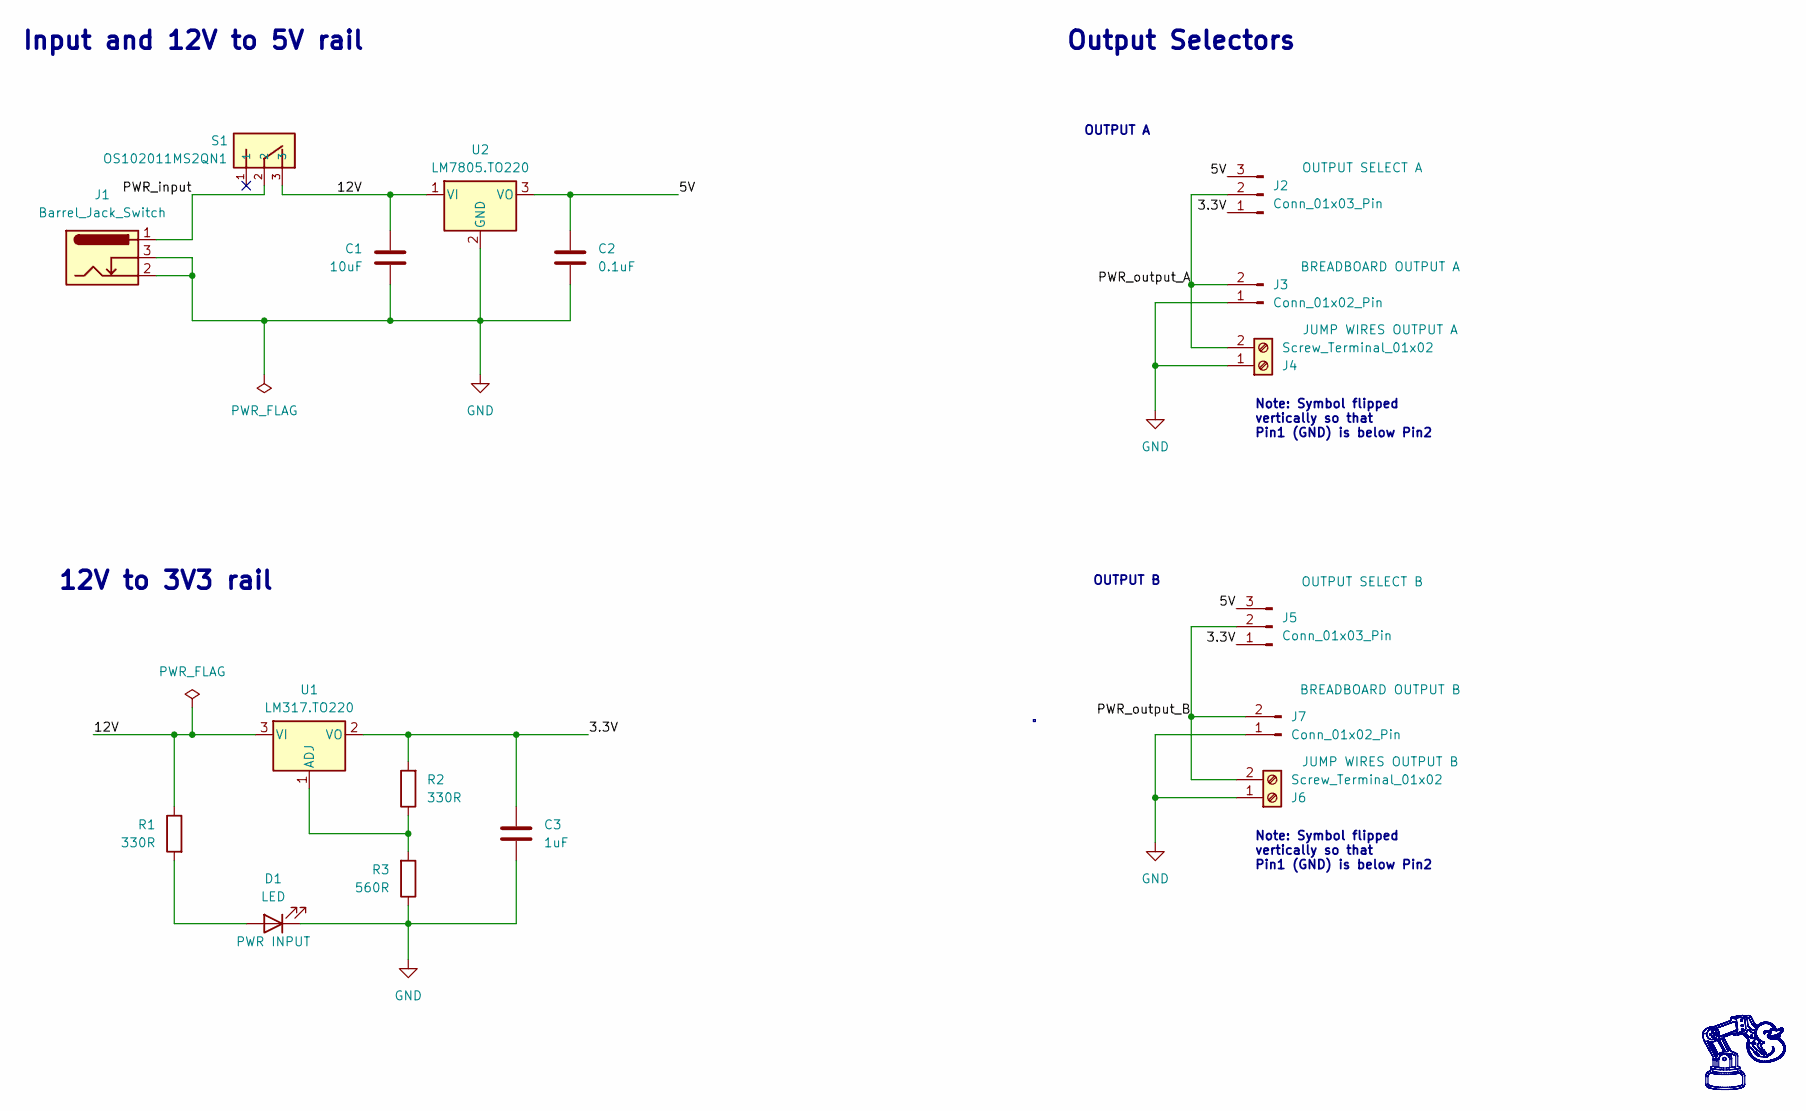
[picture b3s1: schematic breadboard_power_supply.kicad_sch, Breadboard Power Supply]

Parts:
C1: 10uF; C_0603_1608Metric_Pad1.08x0.95mm_HandSolder
C2: 0.1uF; C_0603_1608Metric_Pad1.08x0.95mm_HandSolder
C3: 1uF; C_0603_1608Metric_Pad1.08x0.95mm_HandSolder
D1: LED; LED_D5.0mm
J1: Barrel_Jack_Switch; BarrelJack_Kycon_KLDX-0202-xC_Horizontal
J2, J5: Conn_01x03_Pin; PinHeader_1x03_P2.54mm_Vertical
J3, J7: Conn_01x02_Pin; PinHeader_1x02_P2.54mm_Vertical
J4, J6: Screw_Terminal_01x02; TerminalBlock_bornier-2_P5.08mm
R1, R2: 330R; R_0603_1608Metric_Pad0.98x0.95mm_HandSolder
R3: 560R; R_0603_1608Metric_Pad0.98x0.95mm_HandSolder
S1: OS102011MS2QN1; SW_OS102011MS2QN1
U1: LM317.TO220; TO-220-3_Vertical
U2: LM7805.TO220; TO-220-3_Vertical

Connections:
/3.3V: C3.2, J2.1, J5.1, R2.2, U1.2 (VO)
/5V: C2.2, J2.3, J5.3, U2.3 (VO)
/12V: C1.2, R1.1, S1.3, U1.3 (VI), U2.1 (VI)
/PWR_input: J1.1, S1.2
/PWR_output_A: J2.2, J3.2, J4.2
/PWR_output_B: J5.2, J6.2, J7.2
GND: C1.1, C2.1, C3.1, D1.1 (K), J1.2, J1.3, J3.1, J4.1, J6.1, J7.1, R3.1, U2.2 (GND)
unnamed: D1.2 (A), R1.2
unnamed: R2.1, R3.2, U1.1 (ADJ)

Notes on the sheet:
OUTPUT B
OUTPUT A
Note: Symbol flipped vertically so that Pin1 (GND) is below Pin2
Input and 12V to 5V rail
12V to 3V3 rail
Output Selectors

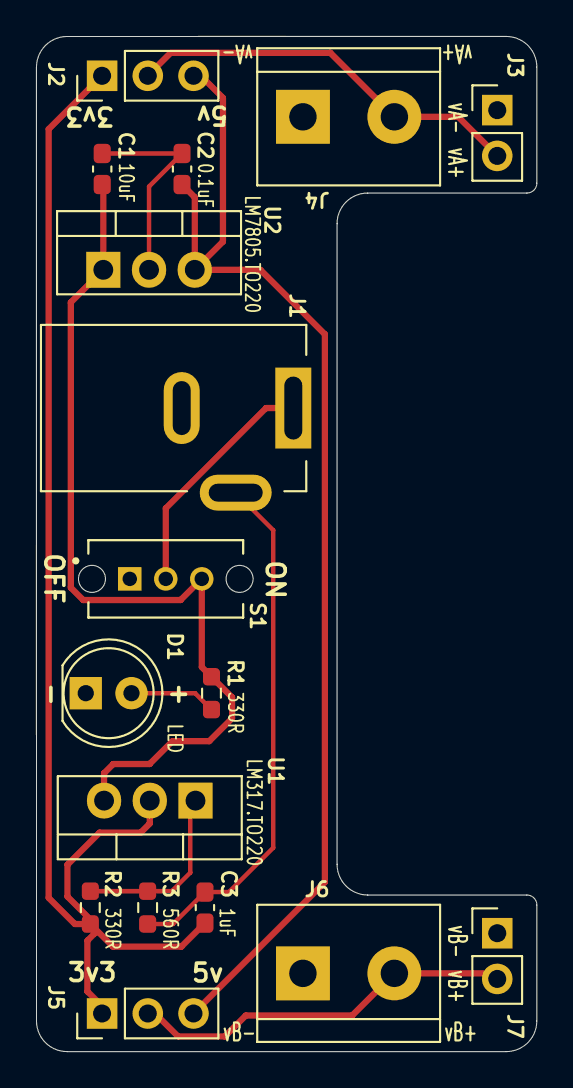
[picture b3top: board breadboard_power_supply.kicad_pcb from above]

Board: 2 copper layers, 27.8 x 56.4 mm, 17 parts (0 on the bottom side), 9 nets.
